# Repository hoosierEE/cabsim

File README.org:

* Cabinet Simulator
This circuit provides a kind of specialized equalization designed to mimic the unique frequency response of a guitar speaker cabinet. Far from a flat or full-range response that you would expect from a Hi-Fi or home theater loudspeaker, a guitar cabinet has a lumpy response of peaks and dips. However, this response is what people expect to hear from a guitar, and it occupies a specific space in the context of a full mix of other instruments.

The response curve of a miked guitar cabinet is a product of the loudspeaker itself, the cabinet size and shape, and the microphone and its placement. This simple analog cabinet simulator does not attempt to replicate every variable, but instead give a reasonable approximation using a minimum number of parts.

** The Circuit
#+caption: schematic
[[file:./cabsim-schematic.png]]

[[https://www.falstad.com/afilter/circuitjs.html?cct=$+0+0.000005+5+55+5+50%0A%25+0+14728.71298666107%0AO+1088+224+1088+176+0%0A170+144+176+144+128+3+20+1000+5+0.1%0Ac+144+176+208+176+0+3.3e-9+0%0Ar+208+176+208+320+0+1000000%0Ar+416+240+480+240+0+10000%0Ar+480+240+544+240+0+10000%0Ac+480+240+480+320+0+1e-8+0%0Ac+416+192+544+192+0+3.3e-10+0%0Aw+544+192+544+240+0%0Ag+256+320+256+336+0%0Aw+576+224+576+272+0%0Ac+576+384+576+432+0+1e-7+0%0Ac+576+432+576+480+0+1e-8+0%0Ar+576+432+720+432+0+330%0Aa+624+496+720+496+1+15+-15+1000000%0Aw+720+432+720+496+0%0Aw+576+480+624+480+0%0Ar+576+480+576+560+0+10000%0Aw+624+512+624+544+0%0Aw+624+544+720+544+0%0Aw+720+544+720+496+0%0Aw+704+272+704+320+0%0Ac+704+320+576+320+0+3.3e-9+0%0Aa+448+496+544+496+1+15+-15+1000000%0Ar+400+480+400+560+0+10000%0Ac+400+480+400+432+0+1e-7+0%0Ac+400+432+400+384+0+0.000001+0%0Ar+544+432+400+432+0+1000%0Aw+544+432+544+496+0%0Aw+448+512+448+544+0%0Aw+544+544+448+544+0%0Aw+544+496+544+544+0%0A174+576+320+528+384+0+1000+0.9950000000000001+res%0Aw+528+272+576+272+0%0Aw+400+560+576+560+0%0Aw+576+320+576+272+0%0Aa+832+496+928+496+1+15+-15+1000000%0Ac+784+480+784+432+0+1e-8+0%0Aw+832+512+832+544+0%0Aw+928+544+832+544+0%0Aw+928+544+928+496+0%0Ar+784+480+784+560+0+330000%0Aw+832+480+784+480+0%0Aw+928+496+928+432+0%0Ar+928+432+784+432+0+330%0Ac+784+368+784+432+0+1e-8+0%0Aa+320+192+416+192+1+15+-15+1000000%0Aw+320+208+320+240+0%0Aw+416+240+416+192+0%0Aw+208+176+320+176+0%0Aw+528+352+528+272+0%0Ag+784+560+784+592+0%0Aw+576+384+400+384+0%0Aw+400+480+448+480+0%0Ar+320+240+416+240+0+10000%0Aw+320+240+320+288+0%0Ac+320+288+416+288+0+3.3e-9+0%0Aw+416+288+416+240+0%0Ac+256+320+256+240+0+1e-7+0%0Ar+320+240+256+240+0+3300%0Aw+704+272+704+208+0%0Aa+576+208+704+208+1+15+-15+1000000%0Aw+544+192+576+192+0%0Ar+704+208+784+208+0+10000%0Aa+912+224+1008+224+1+15+-15+1000000%0Aw+912+208+864+208+0%0Aw+912+240+912+304+0%0Aw+1008+304+1008+224+0%0Aw+256+320+480+320+0%0Aw+208+320+256+320+0%0Ar+704+272+576+272+0+3300%0Aw+576+560+784+560+0%0A174+864+208+832+304+0+10000+0.9851000000000001+level%0Ag+832+256+832+304+0%0Ar+864+304+912+304+0+10000%0Ar+912+304+1008+304+0+10000%0Aw+912+304+912+352+0%0Ac+912+352+1008+352+0+3.3e-9+0%0Aw+1008+352+1008+304+0%0Ax+406+355+520+358+0+16+resonance+(c1k)%0Ax+943+158+1025+161+0+16+level+(a10k)%0Ac+1008+224+1088+224+0+0.000001+0%0Ar+1088+224+1088+320+0+10000%0Ag+1088+320+1088+336+0%0Ac+784+208+864+208+0+1e-7+0%0Ar+784+272+784+368+0+2200%0Aw+784+368+752+368+0%0As+752+368+752+272+0+0+false%0Aw+784+272+752+272+0%0Aw+784+272+784+208+0%0Ao+1+16+0+34+5+0.00009765625+0+-1+in%0Ao+0+16+0+34+2.5+0.00009765625+1+-1+out%0A][simulation]]

Starting with a high input impedance (~1MΩ) suitable for a passive electric guitar pickup, the input stage starts with a gain of about 3.5x that falls off with a first-order highpass response below about 750Hz.

After the input gain stage is a bridged-T notch filter at around 9kHz. The notch isn't the goal, rather the 2nd-order sloping lowpass filter from 2kHz-9kHz. This is a steep roll-off which would normally be achieved with a 2nd- or 3rd-order active filter. But later parts of the circuit will further attenuate the highs above 9kHz so this trick achieves most of the response with fewer components.

Following the notch is an active gyrator stage. Two resonant impedance converters (gyrators) tuned to 150Hz and 2.8kHz respectively create two broad peaks. A "resonance" control allows the user to dampen or increase the contribution of these two peaks to the overall signal.

Next comes another active gyrator, but this one acts as a notch rather than a peak, sharply cutting high midrange at around 1.5kHz. This notch aims to simulate the comb filtering of the speaker cone that a close microphone picks up.

Finally an output gain stage provides an active "level" control to adjust volume, providing up to 22dB of overall gain at 2.5kHz.

For the circuit tweaking enthusiasts out there, here is an illustration of which parts of the circuit are responsible for which parts of the frequency response:

#+caption: illustrated frequency response
[[file:./cabsim-filters.png]]

** Component Values
One of my design goals is to use as few different comoponent values as possible without sacrificing functionality. This makes it easier to buy components in bulk if you only need to have a small handful of different values. In this circuit, you might notice there are a lot of 10kΩ resistors and 10nF and 100nF capacitors. But it's not always feasible to just use values where the most significant digit is =1=. So there are also some 3.9kΩ resistors and 330pF and 3.3nF capacitors. My working theory is that the optimal balance between expressivity and using the minimum number of different values is to have a set of values that are multiples of =1=, and =3.3=. I fell short of that goal in this circuit by including 2.2nF and 3.9kΩ values, but the vast majority of values are multiples of =1=, so that gives me some warm fuzzy feelings.

** Frequency Response
The frequency response of this circuit touches on the key aspects of a typical guitar speaker and speaker cabinet: first order highpass around 200Hz, 2nd order lowpass around 5kHz, and a slight notch between 1kHz and 2kHz.

#+caption: resonance = 0
[[file:./cabsim-r0.0.png]]
#+caption: resonance = 0.5
[[file:./cabsim-r0.5.png]]
#+caption: resonance = 1
[[file:./cabsim-r1.0.png]]

For comparison, Celestion [[https://celestion.com/product/vintage-30/][publishes]] a frequency response plot of their Vintage 30 loudspeaker that looks like this:

#+caption: vintage 30
[[file:./T3903-Vintage-30-copy.jpg]]
** Possible Modifications
As shown, this circuit is stripped-down to the essentials. But there are some minor mods you can do to make it more flexible.

#+caption: de-notch
[[file:./cabsim-mod.png]]

For example, partially disabling the 2.5kHz notch will change the character noticeably and only costs one switch and one resistor.

** 1590a Layout
This repo contains KiCad files for a circuit board layout intended to fit inside a 1590a-sized enclosure.

Circuit board layers:
[[file:./cabsim-board.png]]

3D Renders:
[[file:./cabsim-render.png]]

[[file:./cabsim-render-bottom.png]]

* Why Cabsim?
Here are a couple reasons to use a cabinet simulator:
1. You are going "ampless" and relying on PA monitors instead of guitar amplifiers. This eliminates some of the heaviest and most cumbersome gear a guitarist deals with, and keeps stage volumes more manageable.
2. You're recording with an audio interface but want to monitor your raw track, and the direct headphone out of the interface sounds bad. A cabsim can make it sound closer to how a guitar cabinet should sound, which will sound more natural in your headphones and hopefully make recording a more pleasant process.
3. You want a headphone setup for silent practice, but the raw signal coming out of your pedals is much too harsh. This cabsim will roll off the highs and give a bit of character so it sounds less flat and sterile.
   
* What Alternatives Exist?
A cabinet simulator is really just a kind of EQ, so naturally if you have an EQ pedal already, you can use it to do the job of a cabinet simulator.

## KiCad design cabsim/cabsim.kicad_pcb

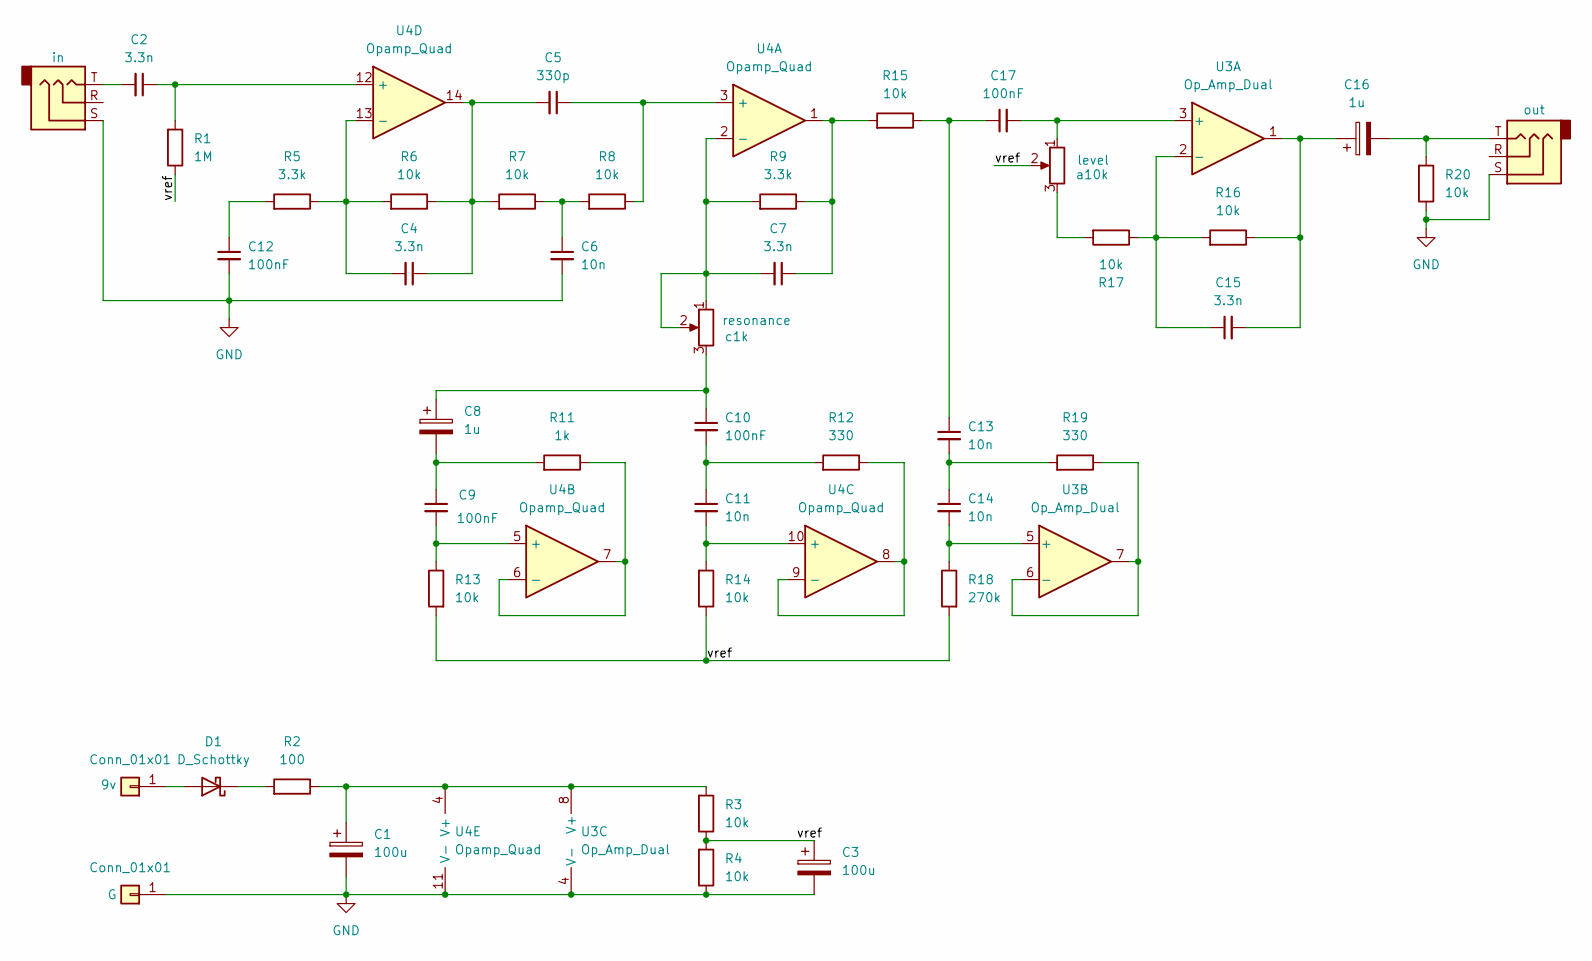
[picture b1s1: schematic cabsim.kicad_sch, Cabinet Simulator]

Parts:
C1, C3: 100u; CP_ELCO_1x2_S
C2, C4, C7, C15: 3.3n; C_CERAMIC_1x2
C5: 330p; C_CERAMIC_1x2
C6, C11, C13, C14: 10n; C_CERAMIC_1x2
C8, C16: 1u; CP_ELCO_1x2_S
C9, C10, C12, C17: 100nF; C_CERAMIC_1x2
D1: D_Schottky; D_DO-41_SOD81_P7.62mm_Horizontal
J1, J5: NJ3FD-V; jack-low-profile
J3, J4: Conn_01x01; PAD_1_std_sqr
R1: 1M; R_1x4
R2: 100; R_1x4
R3, R4, R6, R7, R8, R13, R14, R15, R16, R17, R20: 10k; R_1x4
R5, R9: 3.3k; R_1x4
R11: 1k; R_1x4
R12, R19: 330; R_1x4
R18: 270k; R_1x4
RV1: c1k; pot-16mm-short-leg
RV2: a10k; pot-16mm-short-leg
U3: Op_Amp_Dual; DIP-8
U4: Opamp_Quad; DIP-14

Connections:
/vref: C3.1, R1.2, R3.2, R4.1, R13.1, R14.2, R18.1, RV2.2
GND: C1.2, C3.2, C6.2, C12.2, J1.S, J4.1, J5.S, R4.2, R20.2, U3.4 (V-), U4.11 (V-)
unnamed: C2.2, J5.T
unnamed: C4.1, C5.2, R6.2, R7.1, U4.14
unnamed: C6.1, R7.2, R8.1
unnamed: C7.1, R9.2, R15.1, U4.1
unnamed: C8.2, C9.1, R11.1
unnamed: C8.1, C10.1, RV1.3
unnamed: C10.2, C11.1, R12.1
unnamed: C12.1, R5.1
unnamed: C13.1, C17.1, R15.2
unnamed: C13.2, C14.1, R19.1
unnamed: C15.2, C16.1, R16.2, U3.1
unnamed: C16.2, J1.T, R20.1
unnamed: D1.2 (A), J3.1
unnamed: D1.1 (K), R2.1
unnamed: R17.1, RV2.3
unnamed: C17.2, RV2.1, U3.3 (+)
unnamed: C15.1, R16.1, R17.2, U3.2 (-)
unnamed: C14.2, R18.2, U3.5 (+)
unnamed: R19.2, U3.6 (-), U3.7
unnamed: C1.1, R2.2, R3.1, U3.8 (V+), U4.4 (V+)
unnamed: C5.1, R8.2, U4.3 (+)
unnamed: C7.2, R9.1, RV1.1, RV1.2, U4.2 (-)
unnamed: C9.2, R13.2, U4.5 (+)
unnamed: R11.2, U4.6 (-), U4.7
unnamed: C11.2, R14.1, U4.10 (+)
unnamed: R12.2, U4.8, U4.9 (-)
unnamed: C2.1, R1.1, U4.12 (+)
unnamed: C4.2, R5.2, R6.1, U4.13 (-)

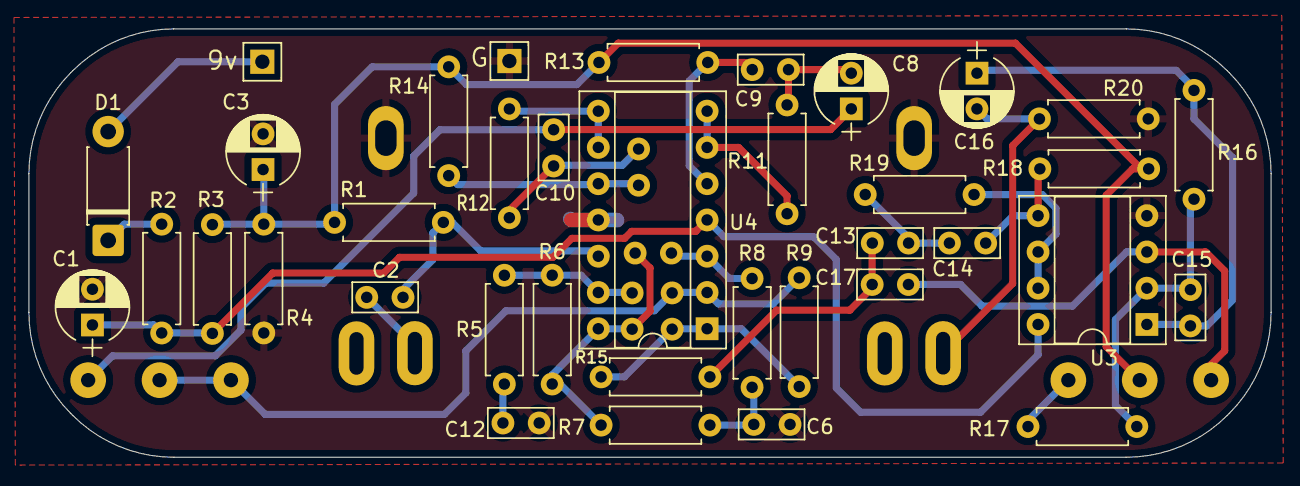
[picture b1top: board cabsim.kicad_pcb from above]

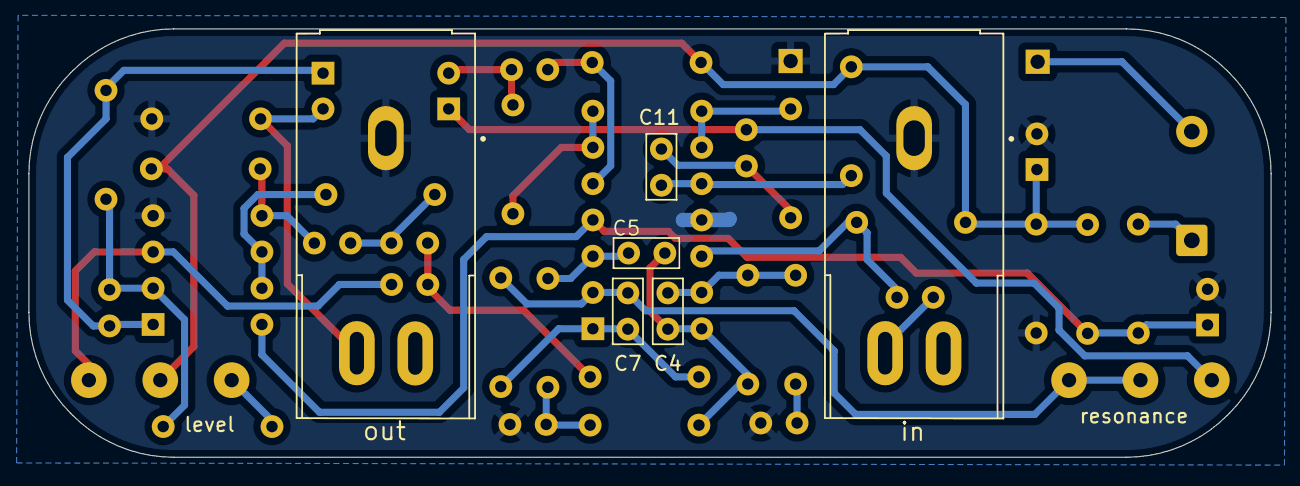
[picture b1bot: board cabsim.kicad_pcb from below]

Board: 2 copper layers, 87.0 x 30.0 mm, 45 parts (8 on the bottom side), 30 nets.

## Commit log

2026-03-04 link and words
2026-03-04 update pcb
2026-03-04 add .gitignore
2026-03-04 update gitignore
2026-03-04 add illustration of filter frequency response
2026-03-06 update pcb and gitignore
2026-03-06 minor routing adjustments
2026-03-06 add layout and render
2026-03-06 add render of other side
2026-03-09 resize jpg
2026-03-10 Create LICENSE
